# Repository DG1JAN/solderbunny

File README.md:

# solderbunny
A PCB to learn soldering for younger kids

## BOM
2x 47 Ohm (0207)</br>
2x 15 kOhm (0270) can also be 10 - 25kOhm (will verry blinking frequency)</br>
2x LED 5mm </br>
2x BC546 (TO92 NPN, also 547,548 etc is fine)</br>
2x 42uF Capaciator (Elko)</br>
1x 3V Battery+Housing (e.g. CR2032, 2x1,5V AA,..)</br>

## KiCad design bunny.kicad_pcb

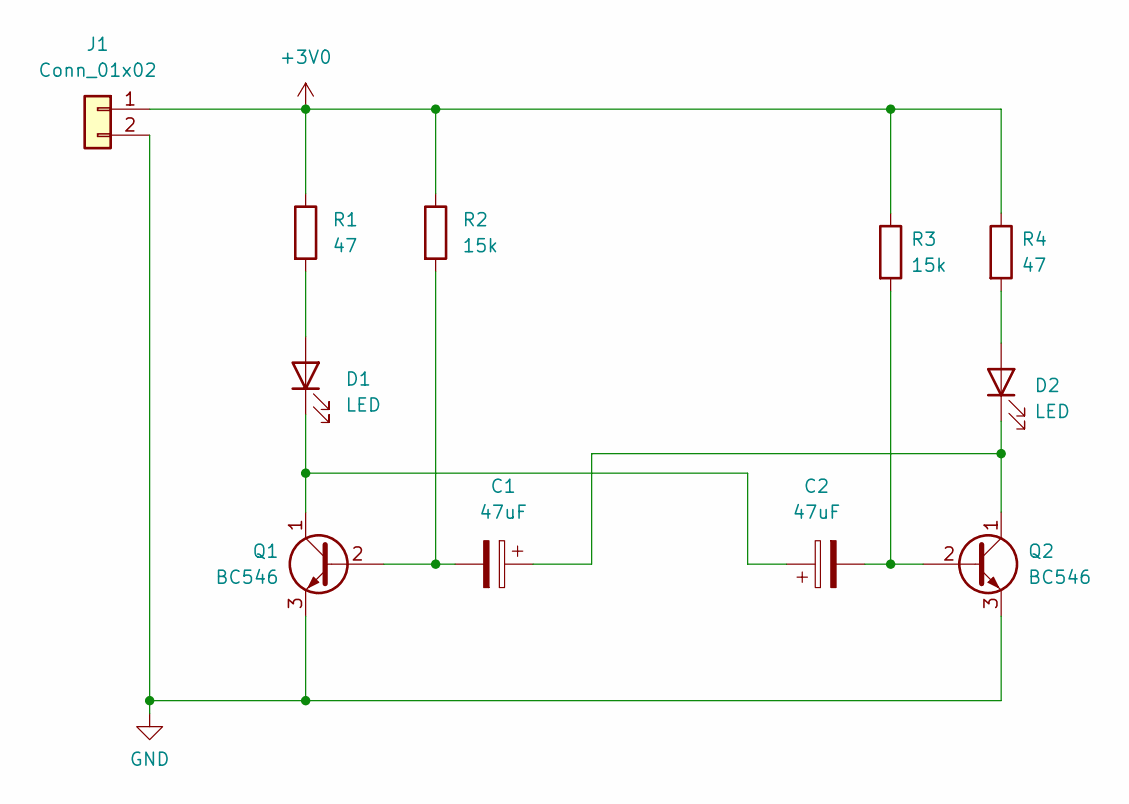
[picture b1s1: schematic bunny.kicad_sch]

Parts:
C1, C2: 47uF; CP_Radial_D5.0mm_P2.50mm
D1, D2: LED; LED_D5.0mm
J1: Conn_01x02; PinSocket_1x02_P2.54mm_Vertical
Q1, Q2: BC546; TO-92_Inline
R1, R4: 47; R_Axial_DIN0207_L6.3mm_D2.5mm_P10.16mm_Horizontal
R2, R3: 15k; R_Axial_DIN0207_L6.3mm_D2.5mm_P10.16mm_Horizontal

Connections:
+3V0: J1.1, R1.1, R2.1, R3.1, R4.1
GND: J1.2, Q1.3 (E), Q2.3 (E)
unnamed: C1.1, D2.1 (K), Q2.1 (C)
unnamed: C1.2, Q1.2 (B), R2.2
unnamed: C2.1, D1.1 (K), Q1.1 (C)
unnamed: C2.2, Q2.2 (B), R3.2
unnamed: D1.2 (A), R1.2
unnamed: D2.2 (A), R4.2

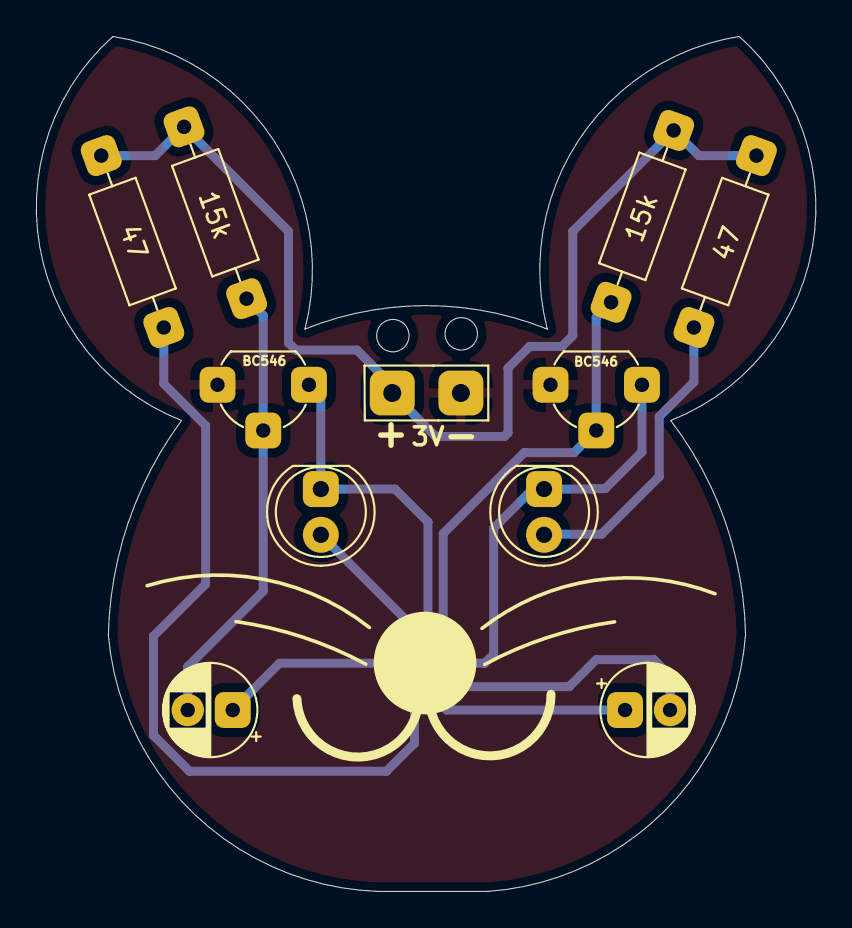
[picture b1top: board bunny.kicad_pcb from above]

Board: 2 copper layers, 43.3 x 47.5 mm, 11 parts (0 on the bottom side), 8 nets.

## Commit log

2023-03-08 Initial Upload v1.0

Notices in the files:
bunny.kicad_pcb:
Creative Commons 4.0 BY-SA
